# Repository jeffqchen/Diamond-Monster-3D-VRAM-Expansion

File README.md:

# Diamond Monster 3D 3Dfx Voodoo 1 VRAM Expansion Mod

The Diamond Monster 3D card is a 3Dfx Voodoo 1.

The Voodoo 1 normally comes with 4MB of RAM in total - 2MB for each of the main chip on the card - FBI (frame buffer interface) and TMU (texture mapping unit).

However, according to 3Dfx documentation, these chips support more than just 2MB of RAM. And extra RAM brings extra capabilities to the card. Therefore, it makes sense to mod the card for the better.

**Thanks to BitsUndBolts, Voodoo 1 cards with socket-spacing RAM chips can be modded with his [3Dfx Voodoo Memory Mod](https://github.com/BitsUndBolts/3Dfx-Voodoo-Memory-Mod).**

However, the Diamond card has a tight chip spacing and his mod can't work on this card. Therefore I had to create this specific one on my own.

The All-in-one long version of the instructions is in [All-in-one README.md](./All-in-one%20README.md).

I've also broken it up into separate pages in the [Wiki](https://github.com/jeffqchen/Diamond-Monster-3D-VRAM-Expansion/wiki) for the ease of navigation.

-----------

# 3D Printed Armor

I designed a 3D printed armor set for this video card. It offers support for the out-most modules of the VRAM modules, which tend to sag due to the lack of support.

Link: [Printables Page](https://www.printables.com/model/723624)

-----------

# Special Thanks

BitsUndBolts
- [Twitter](https://twitter.com/BitsUndBolts)
- [YouTube](https://www.youtube.com/@bitsundbolts/)

-----------

Shield: [![CC BY-SA 4.0][cc-by-sa-shield]][cc-by-sa]

This work is licensed under a
[Creative Commons Attribution-ShareAlike 4.0 International License][cc-by-sa].

[![CC BY-SA 4.0][cc-by-sa-image]][cc-by-sa]

[cc-by-sa]: http://creativecommons.org/licenses/by-sa/4.0/
[cc-by-sa-image]: https://licensebuttons.net/l/by-sa/4.0/88x31.png
[cc-by-sa-shield]: https://img.shields.io/badge/License-CC%20BY--SA%204.0-lightgrey.svg

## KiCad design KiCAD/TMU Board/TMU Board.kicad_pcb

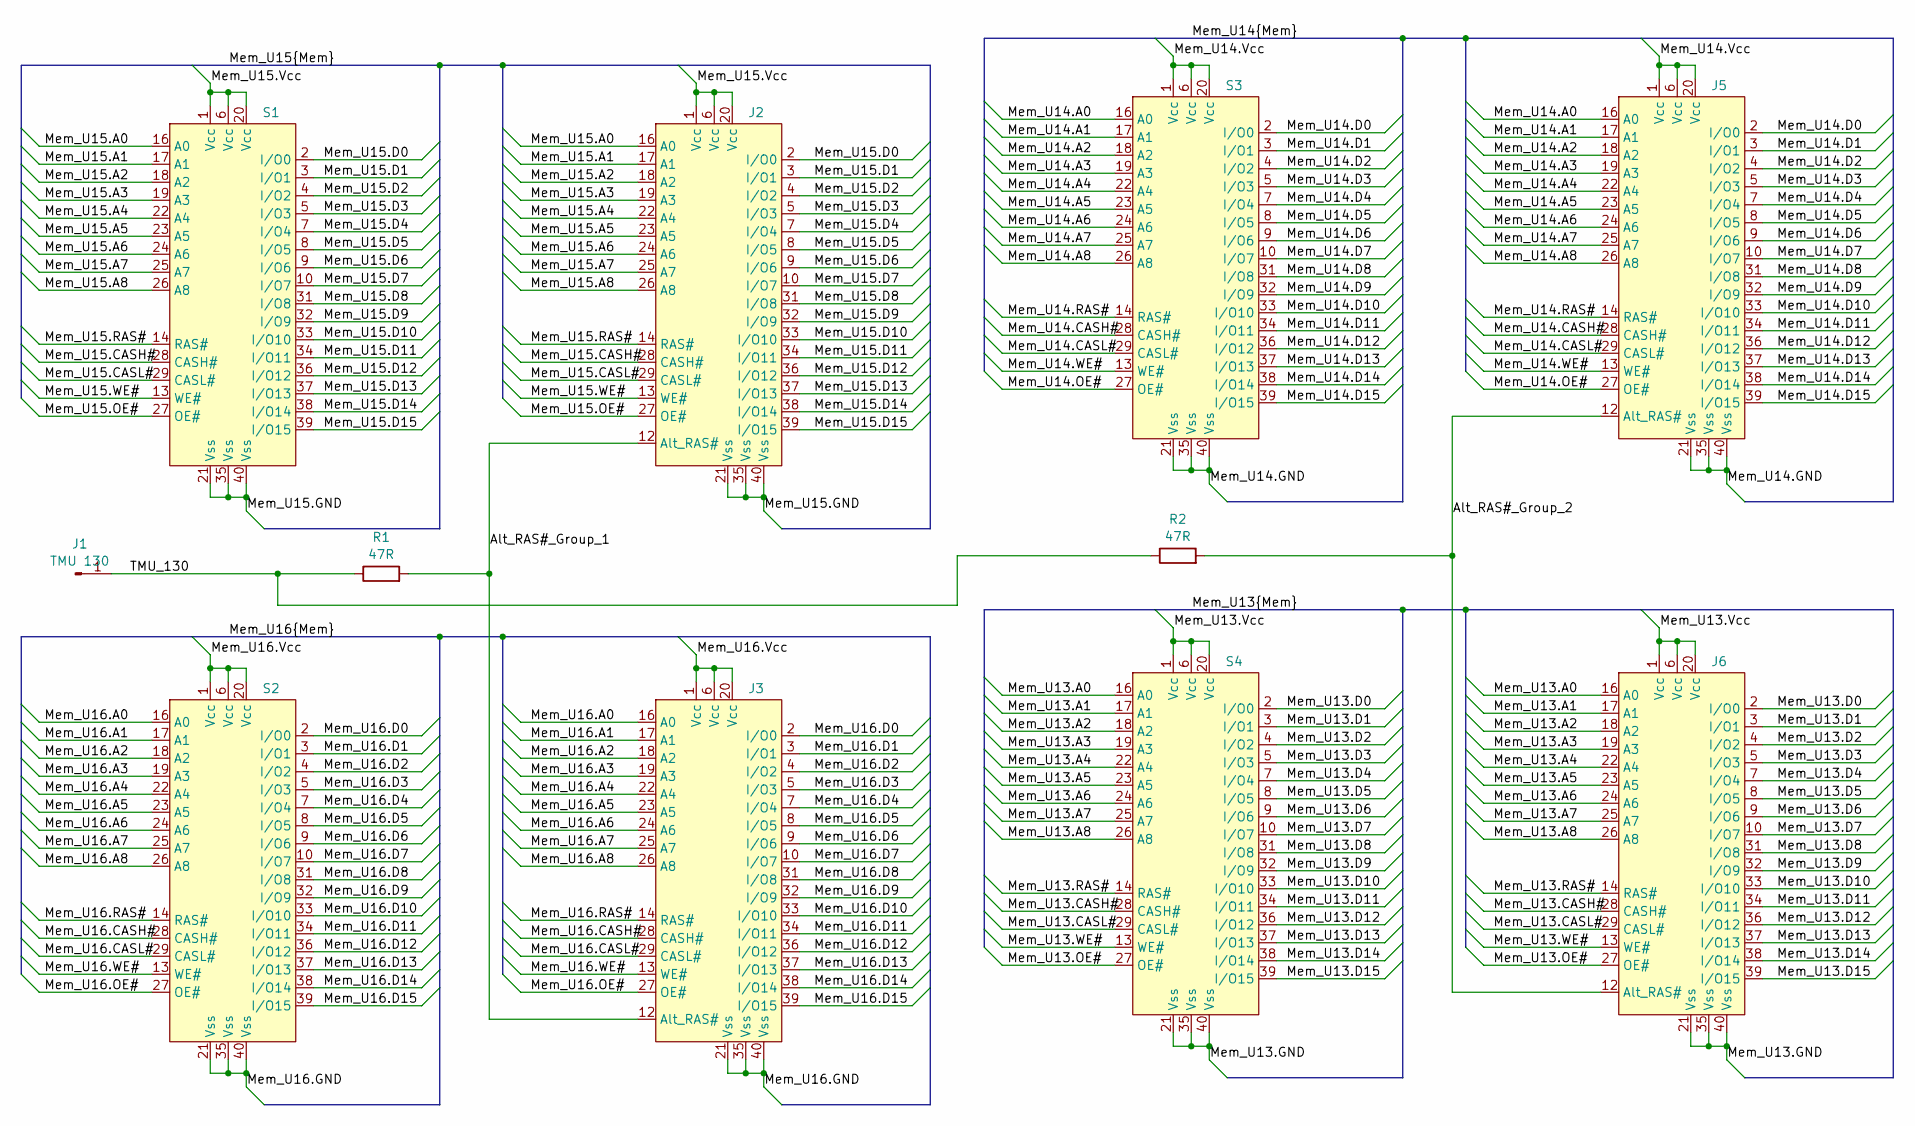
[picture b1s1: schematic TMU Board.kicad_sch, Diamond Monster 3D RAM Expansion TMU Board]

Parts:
J1: TMU 130; Single Pad
J2, J3, J5, J6: Pin Header 2x20 SMD Inverted
R1, R2: 47R; R_0805_2012Metric_Pad1.20x1.40mm_HandSolder
S1, S2, S3, S4: SOJ40 Castellated Vias

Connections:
/Alt_RAS#_Group_1: J2.12 (Alt_RAS#), J3.12 (Alt_RAS#), R1.2
/Alt_RAS#_Group_2: J5.12 (Alt_RAS#), J6.12 (Alt_RAS#), R2.2
/Mem_U13.A0: J6.16 (A0), S4.16 (A0)
/Mem_U13.A1: J6.17 (A1), S4.17 (A1)
/Mem_U13.A2: J6.18 (A2), S4.18 (A2)
/Mem_U13.A3: J6.19 (A3), S4.19 (A3)
/Mem_U13.A4: J6.22 (A4), S4.22 (A4)
/Mem_U13.A5: J6.23 (A5), S4.23 (A5)
/Mem_U13.A6: J6.24 (A6), S4.24 (A6)
/Mem_U13.A7: J6.25 (A7), S4.25 (A7)
/Mem_U13.A8: J6.26 (A8), S4.26 (A8)
/Mem_U13.CASH#: J6.28 (CASH#), S4.28 (CASH#)
/Mem_U13.CASL#: J6.29 (CASL#), S4.29 (CASL#)
/Mem_U13.D0: J6.2 (I/O0), S4.2 (I/O0)
/Mem_U13.D1: J6.3 (I/O1), S4.3 (I/O1)
/Mem_U13.D2: J6.4 (I/O2), S4.4 (I/O2)
/Mem_U13.D3: J6.5 (I/O3), S4.5 (I/O3)
/Mem_U13.D4: J6.7 (I/O4), S4.7 (I/O4)
/Mem_U13.D5: J6.8 (I/O5), S4.8 (I/O5)
/Mem_U13.D6: J6.9 (I/O6), S4.9 (I/O6)
/Mem_U13.D7: J6.10 (I/O7), S4.10 (I/O7)
/Mem_U13.D8: J6.31 (I/O8), S4.31 (I/O8)
/Mem_U13.D9: J6.32 (I/O9), S4.32 (I/O9)
/Mem_U13.D10: J6.33 (I/O10), S4.33 (I/O10)
/Mem_U13.D11: J6.34 (I/O11), S4.34 (I/O11)
/Mem_U13.D12: J6.36 (I/O12), S4.36 (I/O12)
/Mem_U13.D13: J6.37 (I/O13), S4.37 (I/O13)
/Mem_U13.D14: J6.38 (I/O14), S4.38 (I/O14)
/Mem_U13.D15: J6.39 (I/O15), S4.39 (I/O15)
/Mem_U13.GND: J6.21 (Vss), J6.35 (Vss), J6.40 (Vss), S4.21 (Vss), S4.35 (Vss), S4.40 (Vss)
/Mem_U13.OE#: J6.27 (OE#), S4.27 (OE#)
/Mem_U13.RAS#: J6.14 (RAS#), S4.14 (RAS#)
/Mem_U13.Vcc: J6.1 (Vcc), J6.6 (Vcc), J6.20 (Vcc), S4.1 (Vcc), S4.6 (Vcc), S4.20 (Vcc)
/Mem_U13.WE#: J6.13 (WE#), S4.13 (WE#)
/Mem_U14.A0: J5.16 (A0), S3.16 (A0)
/Mem_U14.A1: J5.17 (A1), S3.17 (A1)
/Mem_U14.A2: J5.18 (A2), S3.18 (A2)
/Mem_U14.A3: J5.19 (A3), S3.19 (A3)
/Mem_U14.A4: J5.22 (A4), S3.22 (A4)
/Mem_U14.A5: J5.23 (A5), S3.23 (A5)
/Mem_U14.A6: J5.24 (A6), S3.24 (A6)
/Mem_U14.A7: J5.25 (A7), S3.25 (A7)
/Mem_U14.A8: J5.26 (A8), S3.26 (A8)
/Mem_U14.CASH#: J5.28 (CASH#), S3.28 (CASH#)
/Mem_U14.CASL#: J5.29 (CASL#), S3.29 (CASL#)
/Mem_U14.D0: J5.2 (I/O0), S3.2 (I/O0)
/Mem_U14.D1: J5.3 (I/O1), S3.3 (I/O1)
/Mem_U14.D2: J5.4 (I/O2), S3.4 (I/O2)
/Mem_U14.D3: J5.5 (I/O3), S3.5 (I/O3)
/Mem_U14.D4: J5.7 (I/O4), S3.7 (I/O4)
/Mem_U14.D5: J5.8 (I/O5), S3.8 (I/O5)
/Mem_U14.D6: J5.9 (I/O6), S3.9 (I/O6)
/Mem_U14.D7: J5.10 (I/O7), S3.10 (I/O7)
/Mem_U14.D8: J5.31 (I/O8), S3.31 (I/O8)
/Mem_U14.D9: J5.32 (I/O9), S3.32 (I/O9)
/Mem_U14.D10: J5.33 (I/O10), S3.33 (I/O10)
/Mem_U14.D11: J5.34 (I/O11), S3.34 (I/O11)
/Mem_U14.D12: J5.36 (I/O12), S3.36 (I/O12)
/Mem_U14.D13: J5.37 (I/O13), S3.37 (I/O13)
/Mem_U14.D14: J5.38 (I/O14), S3.38 (I/O14)
/Mem_U14.D15: J5.39 (I/O15), S3.39 (I/O15)
/Mem_U14.GND: J5.21 (Vss), J5.35 (Vss), J5.40 (Vss), S3.21 (Vss), S3.35 (Vss), S3.40 (Vss)
/Mem_U14.OE#: J5.27 (OE#), S3.27 (OE#)
/Mem_U14.RAS#: J5.14 (RAS#), S3.14 (RAS#)
/Mem_U14.Vcc: J5.1 (Vcc), J5.6 (Vcc), J5.20 (Vcc), S3.1 (Vcc), S3.6 (Vcc), S3.20 (Vcc)
/Mem_U14.WE#: J5.13 (WE#), S3.13 (WE#)
/Mem_U15.A0: J2.16 (A0), S1.16 (A0)
/Mem_U15.A1: J2.17 (A1), S1.17 (A1)
/Mem_U15.A2: J2.18 (A2), S1.18 (A2)
/Mem_U15.A3: J2.19 (A3), S1.19 (A3)
/Mem_U15.A4: J2.22 (A4), S1.22 (A4)
/Mem_U15.A5: J2.23 (A5), S1.23 (A5)
/Mem_U15.A6: J2.24 (A6), S1.24 (A6)
/Mem_U15.A7: J2.25 (A7), S1.25 (A7)
/Mem_U15.A8: J2.26 (A8), S1.26 (A8)
/Mem_U15.CASH#: J2.28 (CASH#), S1.28 (CASH#)
/Mem_U15.CASL#: J2.29 (CASL#), S1.29 (CASL#)
/Mem_U15.D0: J2.2 (I/O0), S1.2 (I/O0)
/Mem_U15.D1: J2.3 (I/O1), S1.3 (I/O1)
/Mem_U15.D2: J2.4 (I/O2), S1.4 (I/O2)
/Mem_U15.D3: J2.5 (I/O3), S1.5 (I/O3)
/Mem_U15.D4: J2.7 (I/O4), S1.7 (I/O4)
/Mem_U15.D5: J2.8 (I/O5), S1.8 (I/O5)
/Mem_U15.D6: J2.9 (I/O6), S1.9 (I/O6)
/Mem_U15.D7: J2.10 (I/O7), S1.10 (I/O7)
/Mem_U15.D8: J2.31 (I/O8), S1.31 (I/O8)
/Mem_U15.D9: J2.32 (I/O9), S1.32 (I/O9)
/Mem_U15.D10: J2.33 (I/O10), S1.33 (I/O10)
/Mem_U15.D11: J2.34 (I/O11), S1.34 (I/O11)
/Mem_U15.D12: J2.36 (I/O12), S1.36 (I/O12)
/Mem_U15.D13: J2.37 (I/O13), S1.37 (I/O13)
/Mem_U15.D14: J2.38 (I/O14), S1.38 (I/O14)
/Mem_U15.D15: J2.39 (I/O15), S1.39 (I/O15)
/Mem_U15.GND: J2.21 (Vss), J2.35 (Vss), J2.40 (Vss), S1.21 (Vss), S1.35 (Vss), S1.40 (Vss)
/Mem_U15.OE#: J2.27 (OE#), S1.27 (OE#)
/Mem_U15.RAS#: J2.14 (RAS#), S1.14 (RAS#)
/Mem_U15.Vcc: J2.1 (Vcc), J2.6 (Vcc), J2.20 (Vcc), S1.1 (Vcc), S1.6 (Vcc), S1.20 (Vcc)
/Mem_U15.WE#: J2.13 (WE#), S1.13 (WE#)
/Mem_U16.A0: J3.16 (A0), S2.16 (A0)
/Mem_U16.A1: J3.17 (A1), S2.17 (A1)
/Mem_U16.A2: J3.18 (A2), S2.18 (A2)
/Mem_U16.A3: J3.19 (A3), S2.19 (A3)
/Mem_U16.A4: J3.22 (A4), S2.22 (A4)
/Mem_U16.A5: J3.23 (A5), S2.23 (A5)
/Mem_U16.A6: J3.24 (A6), S2.24 (A6)
/Mem_U16.A7: J3.25 (A7), S2.25 (A7)
/Mem_U16.A8: J3.26 (A8), S2.26 (A8)
/Mem_U16.CASH#: J3.28 (CASH#), S2.28 (CASH#)
/Mem_U16.CASL#: J3.29 (CASL#), S2.29 (CASL#)
/Mem_U16.D0: J3.2 (I/O0), S2.2 (I/O0)
/Mem_U16.D1: J3.3 (I/O1), S2.3 (I/O1)
/Mem_U16.D2: J3.4 (I/O2), S2.4 (I/O2)
/Mem_U16.D3: J3.5 (I/O3), S2.5 (I/O3)
/Mem_U16.D4: J3.7 (I/O4), S2.7 (I/O4)
/Mem_U16.D5: J3.8 (I/O5), S2.8 (I/O5)
/Mem_U16.D6: J3.9 (I/O6), S2.9 (I/O6)
/Mem_U16.D7: J3.10 (I/O7), S2.10 (I/O7)
/Mem_U16.D8: J3.31 (I/O8), S2.31 (I/O8)
/Mem_U16.D9: J3.32 (I/O9), S2.32 (I/O9)
/Mem_U16.D10: J3.33 (I/O10), S2.33 (I/O10)
/Mem_U16.D11: J3.34 (I/O11), S2.34 (I/O11)
/Mem_U16.D12: J3.36 (I/O12), S2.36 (I/O12)
/Mem_U16.D13: J3.37 (I/O13), S2.37 (I/O13)
/Mem_U16.D14: J3.38 (I/O14), S2.38 (I/O14)
/Mem_U16.D15: J3.39 (I/O15), S2.39 (I/O15)
/Mem_U16.GND: J3.21 (Vss), J3.35 (Vss), J3.40 (Vss), S2.21 (Vss), S2.35 (Vss), S2.40 (Vss)
/Mem_U16.OE#: J3.27 (OE#), S2.27 (OE#)
/Mem_U16.RAS#: J3.14 (RAS#), S2.14 (RAS#)
/Mem_U16.Vcc: J3.1 (Vcc), J3.6 (Vcc), J3.20 (Vcc), S2.1 (Vcc), S2.6 (Vcc), S2.20 (Vcc)
/Mem_U16.WE#: J3.13 (WE#), S2.13 (WE#)
/TMU_130: J1.1, R1.1, R2.1

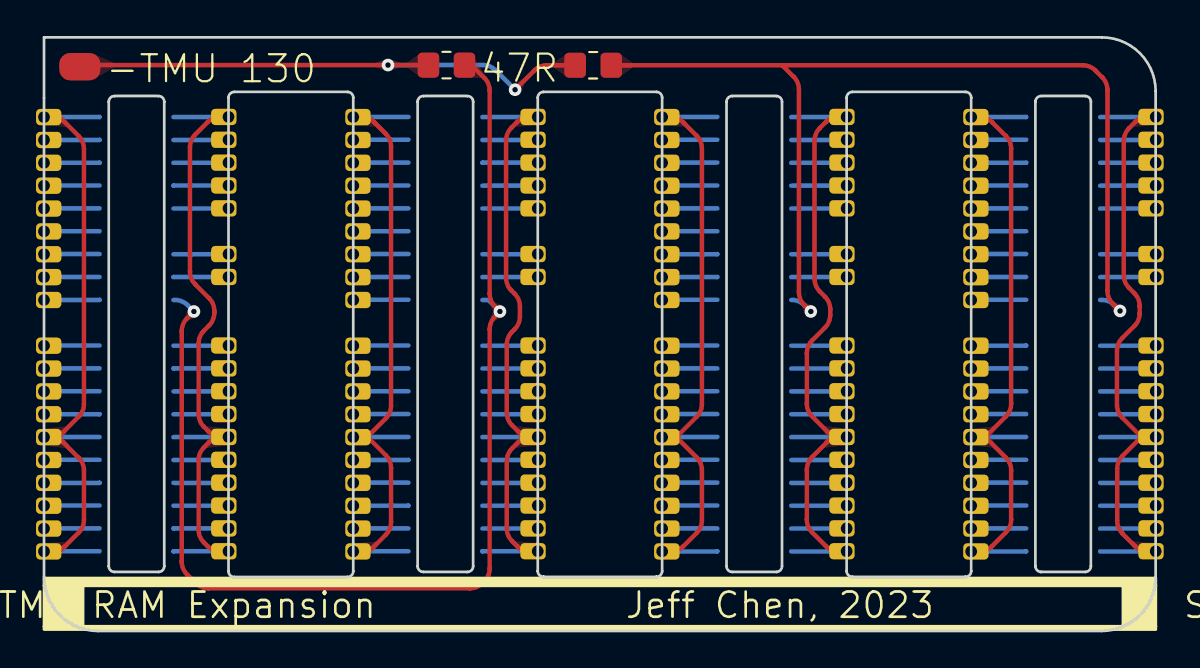
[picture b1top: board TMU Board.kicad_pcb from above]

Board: 2 copper layers, 61.8 x 33.0 mm, 11 parts (0 on the bottom side), 131 nets.

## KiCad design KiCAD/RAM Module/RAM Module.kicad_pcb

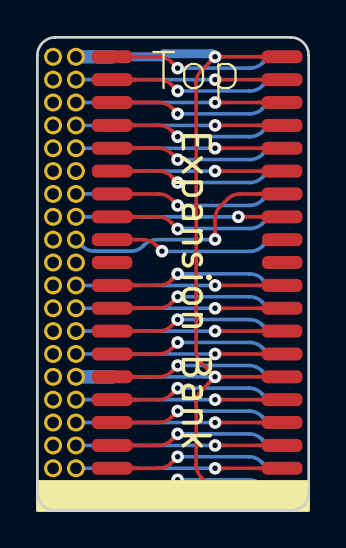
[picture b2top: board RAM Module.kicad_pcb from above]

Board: 4 copper layers, 15.1 x 26.3 mm, 3 parts (1 on the bottom side), 33 nets.

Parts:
P1: Pin Header Male 2x20 THT
U1: Original Bank; SOJ40
U2: Expansion Bank; SOJ40

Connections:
/Shared.A0: P1.16 (A0), U1.16 (A0), U2.16 (A0)
/Shared.A1: P1.17 (A1), U1.17 (A1), U2.17 (A1)
/Shared.A2: P1.18 (A2), U1.18 (A2), U2.18 (A2)
/Shared.A3: P1.19 (A3), U1.19 (A3), U2.19 (A3)
/Shared.A4: P1.22 (A4), U1.22 (A4), U2.22 (A4)
/Shared.A5: P1.23 (A5), U1.23 (A5), U2.23 (A5)
/Shared.A6: P1.24 (A6), U1.24 (A6), U2.24 (A6)
/Shared.A7: P1.25 (A7), U1.25 (A7), U2.25 (A7)
/Shared.A8: P1.26 (A8), U1.26 (A8), U2.26 (A8)
/Shared.CASH#: P1.28 (CASH#), U1.28 (CASH#), U2.28 (CASH#)
/Shared.CASL#: P1.29 (CASL#), U1.29 (CASL#), U2.29 (CASL#)
/Shared.D0: P1.2 (I/O0), U1.2 (I/O0), U2.2 (I/O0)
/Shared.D1: P1.3 (I/O1), U1.3 (I/O1), U2.3 (I/O1)
/Shared.D2: P1.4 (I/O2), U1.4 (I/O2), U2.4 (I/O2)
/Shared.D3: P1.5 (I/O3), U1.5 (I/O3), U2.5 (I/O3)
/Shared.D4: P1.7 (I/O4), U1.7 (I/O4), U2.7 (I/O4)
/Shared.D5: P1.8 (I/O5), U1.8 (I/O5), U2.8 (I/O5)
/Shared.D6: P1.9 (I/O6), U1.9 (I/O6), U2.9 (I/O6)
/Shared.D7: P1.10 (I/O7), U1.10 (I/O7), U2.10 (I/O7)
/Shared.D8: P1.31 (I/O8), U1.31 (I/O8), U2.31 (I/O8)
/Shared.D9: P1.32 (I/O9), U1.32 (I/O9), U2.32 (I/O9)
/Shared.D10: P1.33 (I/O10), U1.33 (I/O10), U2.33 (I/O10)
/Shared.D11: P1.34 (I/O11), U1.34 (I/O11), U2.34 (I/O11)
/Shared.D12: P1.36 (I/O12), U1.36 (I/O12), U2.36 (I/O12)
/Shared.D13: P1.37 (I/O13), U1.37 (I/O13), U2.37 (I/O13)
/Shared.D14: P1.38 (I/O14), U1.38 (I/O14), U2.38 (I/O14)
/Shared.D15: P1.39 (I/O15), U1.39 (I/O15), U2.39 (I/O15)
/Shared.GND: P1.21 (Vss), P1.35 (Vss), P1.40 (Vss), U1.15 (NC_A9), U1.21 (Vss), U1.35 (Vss), U1.40 (Vss), U2.15 (NC_A9), U2.21 (Vss), U2.35 (Vss), U2.40 (Vss)
/Shared.OE#: P1.27 (OE#), U1.27 (OE#), U2.27 (OE#)
/Shared.Vcc: P1.1 (Vcc), P1.6 (Vcc), P1.20 (Vcc), U1.1 (Vcc), U1.6 (Vcc), U1.20 (Vcc), U2.1 (Vcc), U2.6 (Vcc), U2.20 (Vcc)
/Shared.WE#: P1.13 (WE#), U1.13 (WE#), U2.13 (WE#)
Alt_RAS: P1.12 (Alt_RAS#), U2.14 (RAS#)
RAS#: P1.14 (RAS#), U1.14 (RAS#)

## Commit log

2023-09-15 Add readme
2023-09-15 Add license
2023-09-15 Add KiCAD Files
2023-10-14 Update Gerber Files
